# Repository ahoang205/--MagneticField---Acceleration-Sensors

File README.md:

# 🧭 Cảm Biến Từ Trường & Gia Tốc Đo Xa Không Dây (Low-Power Wireless Magnetic & Acceleration Sensing System)

Dự án thiết kế hệ thống phần cứng và phần mềm nhúng (Embedded IoT System) công suất thấp dùng để đo đạc, thu thập dữ liệu **Từ Trường 3 Trục** và **Gia Tốc / Góc Quay 6 Trục**, truyền dữ liệu đo từ xa qua mạng không dây **Wi-Fi Telemetry** về máy chủ giám sát.

---

## ⚡ Tính Năng Hệ Thống (Key Features)

- **Cảm Biến Từ Trường Độ Chính Xác Cao:** Tích hợp chip **MMC5983MA** (3-Axis Magnetometer) đo từ trường trái đất và phát hiện các biến đổi từ tính nhạy bén.
- **Cảm Biến Gia Tốc & Góc Quay Chuẩn Ô Tô:** Tích hợp IMU 6 trục **ASM330LHHTR** (Automotive Grade 6-axis IMU) đo gia tốc tuyến tính và vận tốc góc cực kỳ ổn định.
- **Khóa Mạch Công Suất Thấp (Low-Power Design):** Quản lý nguồn thông minh tối ưu điện năng tiêu thụ cho các thiết bị đo đạc chạy pin / năng lượng mặt trời.
- **Truyền Dữ Liệu Không Dây (Wi-Fi Telemetry):** Vi điều khiển **ESP32** đóng vai trò thu thập dữ liệu qua chuẩn truyền thông **I2C/SPI** và phát dữ liệu Telemetry liên tục qua Wi-Fi.

---

## 🧩 Sơ Đồ Khối Hệ Thống (System Architecture)

```mermaid
flowchart LR
    subgraph Sensors["Hệ Thống Cảm Biến"]
        S1["MMC5983MA (Từ Trường 3 Trục)"]
        S2["ASM330LHHTR (Gia Tốc & Gyro 6 Trục)"]
    end

    subgraph MCU["Xử Lý & Truyền Thông"]
        E1["ESP32 Microcontroller"]
        E2["Mạch Quản Lý Nguồn Năng Lượng Thấp"]
    end

    subgraph Output["Giám Sát Từ Xa"]
        W1["Mạng Wi-Fi Telemetry"]
        D1["Web Dashboard / Server Giám Sát"]
    end

    S1 -- "I2C Bus" --> E1
    S2 -- "I2C / SPI" --> E1
    E2 -- "Power Supply (3.3V)" --> E1
    E1 -- "UDP / MQTT / HTTP Telemetry" --> W1
    W1 --> D1
```

---

## 📊 Thông Số Kỹ Thuật (Specifications)

| Thông Số (Parameter) | Giá Trị (Value) | Ghi Chú (Notes) |
| :--- | :--- | :--- |
| **Vi Điều Khiển Main MCU** | `ESP32 / ESP32-WROOM-32` | Tích hợp Wi-Fi 802.11 b/g/n & Bluetooth |
| **Cảm Biến Từ Trường** | `MMC5983MA` | 0.5 mG resolution, ±8 Gauss FSR |
| **Cảm Biến IMU 6 Trục** | `ASM330LHHTR` | 3-axis Accel + 3-axis Gyro (Automotive) |
| **Chuẩn Truyền Thông Nối Tiếp** | `I2C (400kHz Fast Mode) / SPI` | Giao tiếp độ tin cậy cao |
| **Điện Áp Cấp (VCC)** | `3.3V DC` | Tích hợp LDO điện áp thấp |
| **Phần Mềm EDA Thiết Kế PCB** | `KiCad v6 / v7 / v8` | Sẵn file `.kicad_sch` & `.kicad_pcb` |

---

## 📂 Cấu Trúc Thư Mục Dự Án (Repository Structure)

```text
Magnetic_field_&_Acceleration_Sensors/
├── hardware/                         # Thiết kế phần cứng (Hardware EDA)
│   ├── schematics/                   # File bản vẽ sơ đồ nguyên lý PDF
│   │   └── schematic_Qcomment_24_12_25.pdf
│   ├── kicad/                        # Bộ file nguồn KiCad (.kicad_sch, .kicad_pcb, .kicad_pro)
│   │   ├── Low-Power Instrument.kicad_pcb
│   │   ├── Low-Power Instrument.kicad_sch
│   │   └── production/               # File Gerber gia công PCB, BOM, CPL
│   └── Dependencies/                 # Thư viện footprint & 3D STEP linh kiện
│       ├── ul_MMC5983MA/             # 3D Model & Footprints cảm biến từ trường
│       └── ul_ASM330LHHTR/           # 3D Model & Footprints cảm biến gia tốc
├── firmware/                         # Mã nguồn vi điều khiển kép (Dual MCU)
│   ├── stm32_firmware/               # Mã nguồn STM32L4xx HAL đọc mẫu cảm biến I2C/UART
│   │   ├── Core/Src/main.c           # Chương trình chính xử lý mẫu từ trường & IMU
│   │   └── supercap_test.ioc         # File cấu hình chân STM32CubeMX
│   └── esp32_wifi_telemetry/         # Mã nguồn ESP32 Arduino IDE
│       └── esp32_wifi_telemetry.ino  # Code Server Web 3D Dashboard & WebSocket Telemetry
├── docs/                             # Tài liệu kỹ thuật dự án
├── .gitignore                        # Cấu hình lọc file rác KiCad & IDE
├── LICENSE                           # Giấy phép bản quyền nguồn mở MIT
└── README.md                         # Tài liệu giới thiệu dự án
```

---

## 🛠️ Hướng Dẫn Cài Đặt & Nạp Code (Installation & Flashing Guide)

### 1. Mở & Chỉnh Sửa Phần Cứng (KiCad)
1. Cài đặt phần mềm [KiCad EDA v6+](https://www.kicad.org/).
2. Mở file `hardware/kicad/Low-Power Instrument.kicad_pro` để xem sơ đồ nguyên lý và thiết kế mạch PCB 2 lớp.

### 2. Nạp Code Cho Vi Điều Khiển ESP32
1. Mở phần mềm **Arduino IDE** (hoặc VS Code với PlatformIO).
2. Thêm bo mạch ESP32 và mở file `firmware/esp32_wifi_telemetry/esp32_wifi_telemetry.ino`.
3. Cấu hình thông số Wi-Fi (SSID, Password) và bấm **Upload** để nạp code cho ESP32.

---

## 📜 Giấy Phép (License)

Dự án được phân phối dưới giấy phép [MIT License](LICENSE) - Miễn phí sử dụng, nghiên cứu và phát triển sản phẩm thương mại.

---
*Authored by **Viet Hoang Luong**.*

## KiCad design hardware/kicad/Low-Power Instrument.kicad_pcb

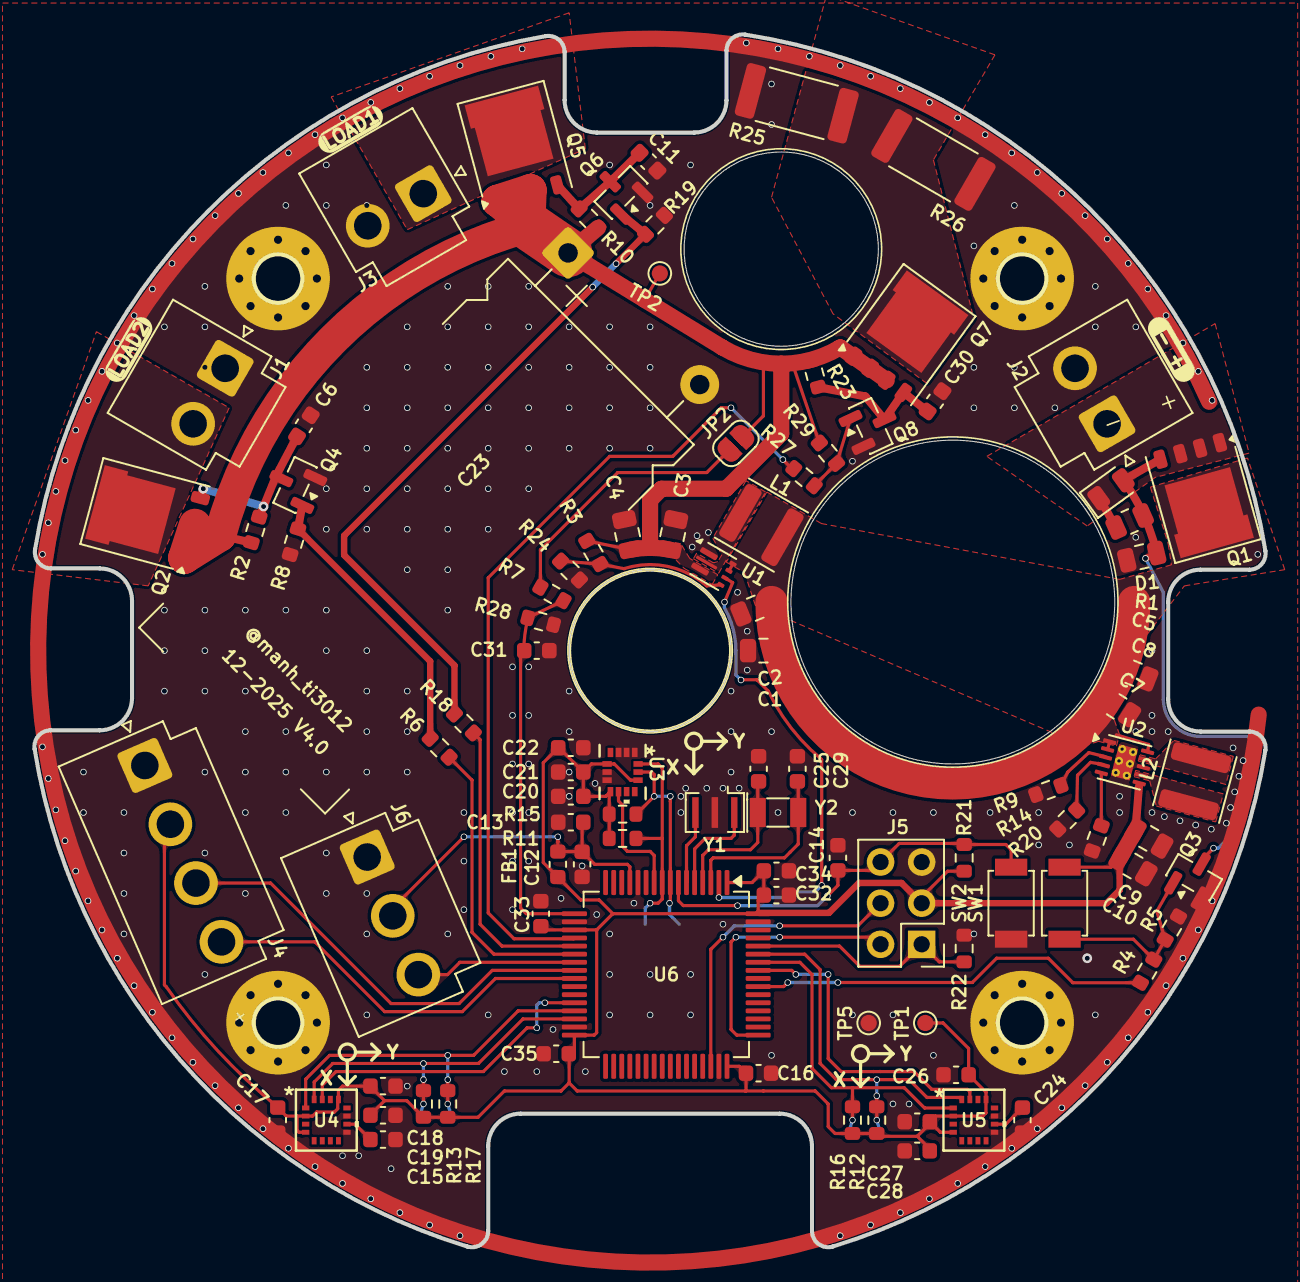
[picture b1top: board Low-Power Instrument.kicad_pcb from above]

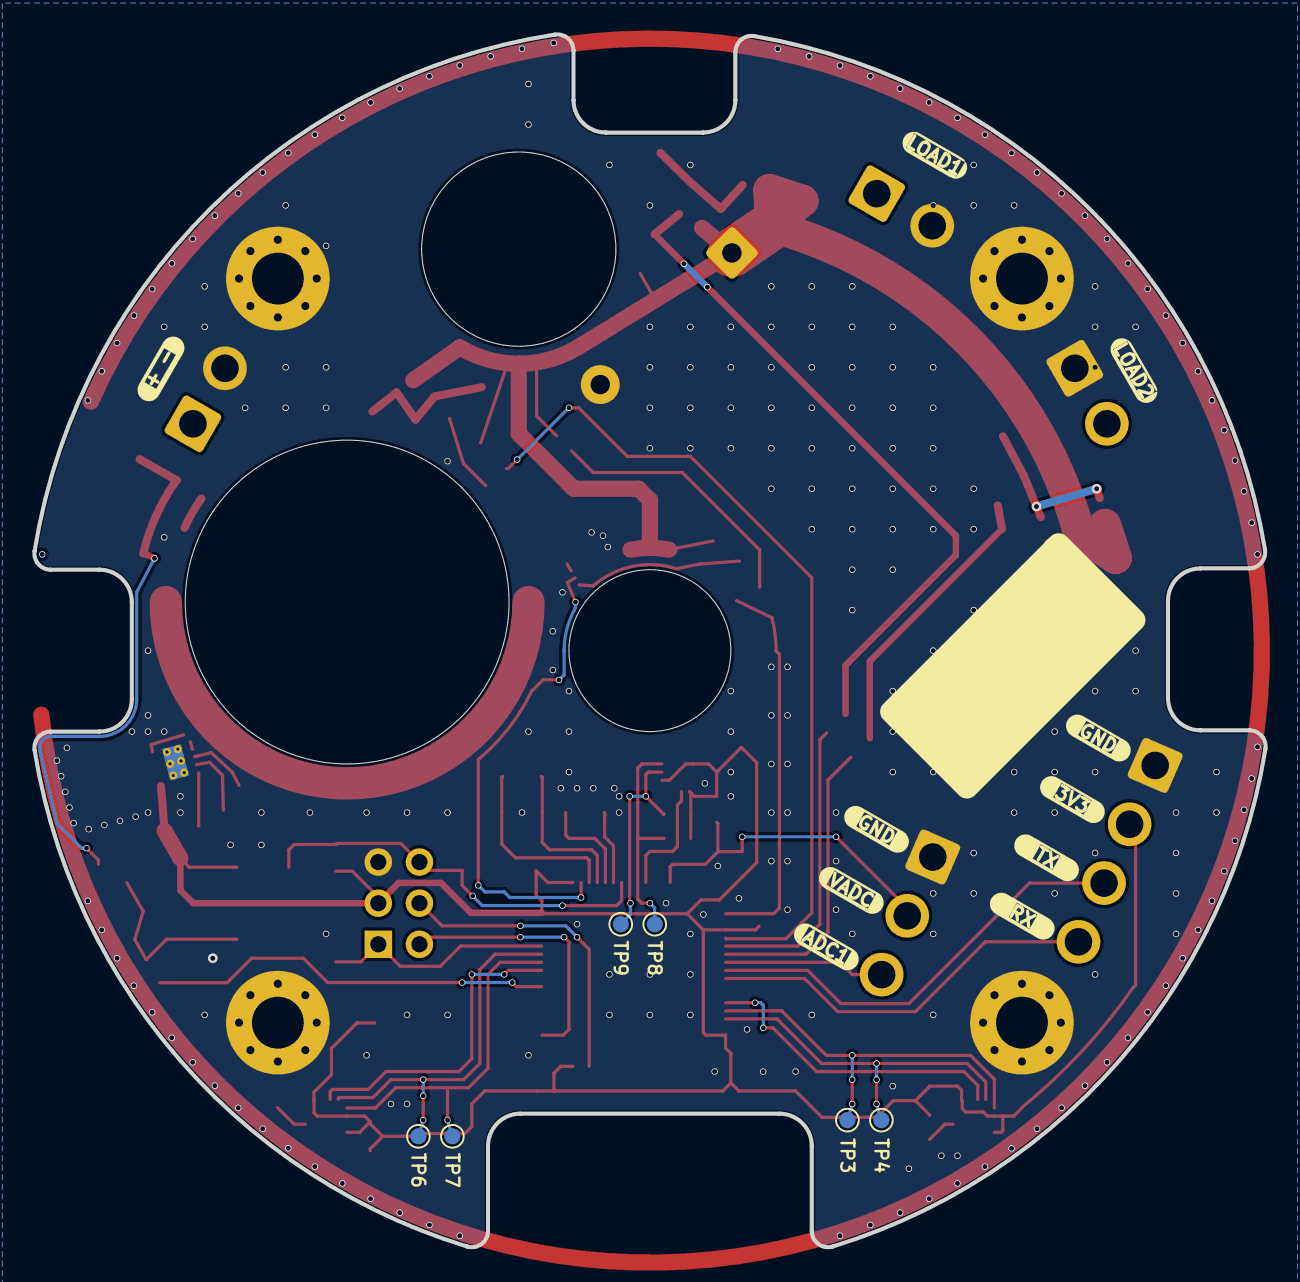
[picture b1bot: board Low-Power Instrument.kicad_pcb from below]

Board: 2 copper layers, 76.0 x 74.9 mm, 106 parts (6 on the bottom side), 53 nets.

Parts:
C1, C2, C3, C4, C5, C7, C8, C9, C10: 22uF; C_0805_2012Metric
C6, C11, C12, C14, C16, C17, C18, C20, C21, C26, C27, C30, C31, C32, C33, C34, C35: 100nF; C_0603_1608Metric
C13, C19, C22, C28: 1uF; C_0603_1608Metric
C15, C24: 10uF; C_0603_1608Metric
C23: 5F; CHP5R5L505R-TWV
C25, C29: 12.5pF; C_0603_1608Metric
D1: Diode; D_0805_2012Metric
FB1: Ferrite Bead; L_0603_1608Metric
H1, H2, H3, H4: MountingHole_Pad; MountingHole_3.2mm_M3_Pad_Via
J1, J2, J3: POWER; JST_VH_B2P-VH_1x02_P3.96mm_Vertical
J4: UART; JST_VH_B4P-VH-B_1x04_P3.96mm_Vertical
J5: DEBUG; PinHeader_2x03_P2.54mm_Vertical
J6: ADC; JST_VH_B3P-VH-B_1x03_P3.96mm_Vertical
JP2: Jumper_2_Open; SolderJumper-2_P1.3mm_Open_RoundedPad1.0x1.5mm
L1: 1uH; L_APV_ANR4020
L2: 2.2uH; L_APV_ANR4020
Q1, Q2, Q5, Q7: DON60P03; PQFN-8-EP_6x5mm_P1.27mm_Generic
Q3, Q4, Q6, Q8: AO3400; SOT-23
R1: 100K; R_0805_2012Metric
R2, R5, R7, R8, R10, R19, R21, R22, R23, R29: 100K; R_0603_1608Metric
R3: 732K; R_0603_1608Metric
R4, R6, R18, R27: 10K; R_0603_1608Metric
R9, R20: 36.5K; R_0603_1608Metric
R11, R12, R13, R15, R16, R17: 4.7K; R_0603_1608Metric
R14: 1.15K; R_0603_1608Metric
R24, R28: 200K; R_0603_1608Metric
R25, R26: 100R; R_2512_6332Metric
SW1, SW2: SW_Push; SW_SPST_B3U-1000P
TP1, TP2, TP3, TP4, TP5, TP6, TP7, TP8, TP9: TestPoint; TestPoint_Pad_D1.0mm
U1: TPS61022; Texas_RWU0007A_VQFN-7_2x2mm_P0.5mm
U2: TPS63900; WSON-10-1EP_2.5x2.5mm_P0.5mm_EP1.2x2mm_ThermalVias
U3: ASM330LHHTR; LGA-14L_2P5X3X0P83_STM
U4, U5: MMC5983MA; MMC5983MA_MEM
U6: STM32L476RGTx; LQFP-64_10x10mm_P0.5mm
Y1: 8Mhz; Resonator_SMD_Murata_CSTxExxV-3Pin_3.0x1.1mm
Y2: 32kHz; Crystal_SMD_3215-2Pin_3.2x1.5mm

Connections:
5V_ENABLE: U1.5 (EN), U6.2 (PC13)
+3.3V: C9.1, C10.1, C16.1, C17.1, C18.1, C19.1, C20.1, C21.1, C22.1, C26.1, C27.1, C28.1, C32.1, C33.1, C34.1, C35.1, FB1.1, J4.2, J5.3, R11.2, R12.2, R13.2, R15.2, R16.2, R17.2, R21.2, SW1.2, TP1.1, U2.6 (VOUT), U3.5 (VDD_IO), U3.8 (VDD), U3.12 (CS), U4.2 (VDD), U4.4 (SPI_CS), U4.13 (VDDIO), U5.2 (VDD), U5.4 (SPI_CS), U5.13 (VDDIO), U6.1 (VBAT), U6.19 (VDD), U6.32 (VDD), U6.48 (VDDUSB), U6.64 (VDD)
+5V: C3.1, C4.1, C23.1, JP2.2 (B), Q2.1 (S), Q2.2 (S), Q2.3 (S), Q5.1 (S), Q5.2 (S), Q5.3 (S), Q7.1 (S), Q7.2 (S), Q7.3 (S), R2.1, R3.2, R10.1, R23.1, R29.2, TP2.1, U1.3 (VOUT)
+BATT: D1.1 (K), J2.1, Q1.1 (S), Q1.2 (S), Q1.3 (S), R1.1
ADC1: J6.3, U6.23 (PA7)
BOOT0: J5.1, R22.2, U6.60 (BOOT0)
DISCHARGE: R27.1, U6.20 (PA4)
GND: C1.2, C2.2, C3.2, C4.2, C5.2, C6.2, C7.2, C8.2, C9.2, C10.2, C11.2, C12.2, C13.2, C14.1, C15.2, C16.2, C17.2, C18.2, C19.2, C20.2, C21.2, C22.2, C23.2, C24.2, C25.2, C26.2, C27.2, C28.2, C29.1, C30.2, C31.2, C32.2, C33.2, C34.2, C35.2, H1.1, H2.1, H3.1, H4.1, J1.1, J2.2, J3.2, J4.1, J5.5, J6.1, Q3.2 (S), Q4.2 (S), Q6.2 (S), Q8.2 (S), R5.2, R7.1, R8.2, R9.2, R14.2, R19.2, R20.2, R22.1, R25.2, R26.2, R28.2, SW2.2, TP5.1, U1.1 (GND), U2.8 (GND), U2.11 (GND), U3.1 (SDO/SA0), U3.2 (RES), U3.3 (RES), U3.6 (GND), U3.7 (GND), U4.9 (GND), U4.11 (GND), U5.9 (GND), U5.11 (GND), U6.12 (VSSA), U6.18 (VSS), U6.31 (VSS), U6.47 (VSS), U6.63 (VSS), Y1.2
I2C1_INT: U5.15 (INT), U6.57 (PB5)
I2C1_SCL: R16.1, TP7.1, U5.1 (SCL/SPI_SCK), U6.58 (PB6)
I2C1_SDA: R12.1, TP6.1, U5.16 (SDA/SPI_SDI), U6.59 (PB7)
I2C2_INT: U4.15 (INT), U6.28 (PB2)
I2C2_SCL: R17.1, TP3.1, U4.1 (SCL/SPI_SCK), U6.29 (PB10)
I2C2_SDA: R13.1, TP4.1, U4.16 (SDA/SPI_SDI), U6.30 (PB11)
I2C3_INT: U3.9 (INT2), U6.10 (PC2)
I2C3_SCL: R15.1, TP9.1, U3.13 (SCL), U6.8 (PC0)
I2C3_SDA: R11.1, TP8.1, U3.14 (SDA), U6.9 (PC1)
LOAD1_ENABLE: R18.1, U6.21 (PA5)
LOAD2_ENABLE: R6.1, U6.22 (PA6)
NRST: C14.2, J5.6, R21.1, SW2.1, U6.7 (NRST)
unnamed: C5.1, D1.2 (A), Q1.4 (G), Q3.3 (D), R1.2
unnamed: J1.2, Q2.5 (D)
unnamed: J3.1, Q5.5 (D)
unnamed: JP2.1 (A), R24.1
unnamed: C6.1, Q2.4 (G), Q4.3 (D), R2.2
unnamed: Q3.1 (G), R4.1, R5.1, SW1.1
unnamed: Q4.1 (G), R6.2, R8.1
unnamed: C11.1, Q5.4 (G), Q6.3 (D), R10.2
unnamed: Q6.1 (G), R18.2, R19.1
unnamed: Q7.5 (D), R25.1, R26.1
unnamed: C30.1, Q7.4 (G), Q8.3 (D), R23.2
unnamed: Q8.1 (G), R27.2, R29.1
unnamed: R3.1, R7.2, U1.4 (FB)
unnamed: L1.2, U1.2 (SW)
unnamed: R9.1, U2.3 (CFG1)
unnamed: R14.1, U2.4 (CFG2)
unnamed: R20.1, U2.5 (CFG3)
unnamed: L2.2, U2.9 (LX1)
unnamed: L2.1, U2.7 (LX2)
unnamed: C15.1, U4.10 (CAP)
unnamed: C24.1, U5.10 (CAP)
unnamed: C25.1, U6.3 (PC14), Y2.2
unnamed: C29.2, U6.4 (PC15), Y2.1
unnamed: U6.5 (PH0), Y1.1
unnamed: U6.6 (PH1), Y1.3
POWER_ENABLE: R4.2, U6.55 (PB3)
SWCLK: J5.2, U6.49 (PA14)
SWDIO: J5.4, U6.46 (PA13)
UART3_RX: J4.4, U6.25 (PC5)
UART3_TX: J4.3, U6.24 (PC4)
VDC: C1.1, C2.1, C7.1, C8.1, L1.1, Q1.5 (D), U1.6 (MODE), U1.7 (VIN), U2.1 (EN), U2.2 (SEL), U2.10 (VIN)
VDDA: C12.1, C13.1, FB1.2, J6.2, U6.13 (VDDA)
V_SENSE: C31.1, R24.2, R28.1, U6.17 (PA3)

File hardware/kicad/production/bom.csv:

Designator,Footprint,Quantity,Value,LCSC Part #
"C1, C10, C2, C3, C4, C5, C7, C8, C9",0805,9,22uF,
"C11, C12, C14, C16, C17, C18, C20, C21, C26, C27, C30, C31, C32, C33, C34, C35, C6",0603,17,100nF,
"C13, C19, C22, C28",0603,4,1uF,
"C15, C24",0603,2,10uF,
C23,CHP5R5L505R-TWV,1,5F,
"C25, C29",0603,2,12.5pF,
D1,0805,1,Diode,
FB1,0603,1,Ferrite Bead,
"J1, J2, J3",JST_VH_B2P-VH_1x02_P3.96mm_Vertical,3,POWER,
J4,JST_VH_B4P-VH-B_1x04_P3.96mm_Vertical,1,UART,
J5,PinHeader_2x03_P2.54mm_Vertical,1,DEBUG,
J6,JST_VH_B3P-VH-B_1x03_P3.96mm_Vertical,1,ADC,
L1,L_APV_ANR4020,1,1uH,
L2,L_APV_ANR4020,1,2.2uH,
"Q1, Q2, Q5, Q7",PQFN-8-EP_6x5mm_P1.27mm_Generic,4,DON60P03,
"Q3, Q4, Q6, Q8",SOT-23,4,AO3400,
R1,0805,1,100K,
"R10, R19, R2, R21, R22, R23, R29, R5, R7, R8",0603,10,100K,
"R11, R12, R13, R15, R16, R17",0603,6,4.7K,
R14,0603,1,1.15K,
"R18, R27, R4, R6",0603,4,10K,
"R20, R9",0603,2,36.5K,
"R24, R28",0603,2,200K,
"R25, R26",2512,2,100R,
R3,0603,1,732K,
"SW1, SW2",SW_SPST_B3U-1000P,2,SW_Push,
U1,Texas_RWU0007A_VQFN-7_2x2mm_P0.5mm,1,TPS61022,
U2,WSON-10-1EP_2.5x2.5mm_P0.5mm_EP1.2x2mm_ThermalVias,1,TPS63900,
U3,LGA-14L_2P5X3X0P83_STM,1,ASM330LHHTR,
"U4, U5",MMC5983MA_MEM,2,MMC5983MA,
U6,LQFP-64_10x10mm_P0.5mm,1,STM32L476RGTx,
Y1,Resonator_SMD_Murata_CSTxExxV-3Pin_3.0x1.1mm,1,8Mhz,
Y2,Crystal_SMD_3215-2Pin_3.2x1.5mm,1,32kHz,

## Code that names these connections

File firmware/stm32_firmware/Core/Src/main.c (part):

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  HAL_GPIO_WritePin(GPIOC, V5_enable_Pin, GPIO_PIN_SET);
  
  // Tắt xả siêu tụ điện (DISCHARGE = LOW)
  HAL_GPIO_WritePin(GPIOA, Discharge_Pin, GPIO_PIN_RESET);
  
  // Mặc định tắt các tải (Relay/LED) ban đầu
  HAL_GPIO_WritePin(GPIOA, Load1_enable_Pin | Load2_enable_Pin, GPIO_PIN_RESET);

  // Khởi tạo các cảm biến
  MMC5983_Init(&hi2c1); // Mag 2
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    if (USART3->ISR & USART_ISR_NE) {
        USART3->ICR = USART_ICR_NECF;  // Xóa lỗi nhiễu (Noise error)
    }
    // TEST PHẦN CỨNG: Nếu chập chân RX (PC5 / J4 Pin 4) xuống GND, tự động bật LED/Relay để test tiếp xúc
    if ((GPIOC->IDR & GPIO_PIN_5) == 0) {
        HAL_GPIO_WritePin(GPIOA, Load1_enable_Pin | Load2_enable_Pin, GPIO_PIN_SET);
    }
    
    if (USART3->ISR & USART_ISR_RXNE) {
        uint8_t rx_data = (uint8_t)(USART3->RDR & 0xFF);
        if (rx_data == '1') {
            // Bật cả 2 tải để kích relay đóng đèn sáng
            HAL_GPIO_WritePin(GPIOA, Load1_enable_Pin | Load2_enable_Pin, GPIO_PIN_SET);
            HAL_UART_Transmit(&huart3, (uint8_t*)"[DEBUG] STM32 RX 1\r\n", 20, 50);
        } else if (rx_data == '0') {
            // Tắt cả 2 tải
            HAL_GPIO_WritePin(GPIOA, Load1_enable_Pin | Load2_enable_Pin, GPIO_PIN_RESET);
            HAL_UART_Transmit(&huart3, (uint8_t*)"[DEBUG] STM32 RX 0\r\n", 20, 50);
        }
    }
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  __HAL_RCC_GPIOA_CLK_ENABLE();
  __HAL_RCC_GPIOB_CLK_ENABLE();

  /*Configure GPIO pin Output Level for PC13 (V5_enable) */
  HAL_GPIO_WritePin(V5_enable_GPIO_Port, V5_enable_Pin, GPIO_PIN_SET);

  /*Configure GPIO pin Output Level for Discharge and Load Switch control */
  HAL_GPIO_WritePin(Discharge_GPIO_Port, Discharge_Pin, GPIO_PIN_RESET);
  HAL_GPIO_WritePin(GPIOA, Load1_enable_Pin|Load2_enable_Pin, GPIO_PIN_RESET);

  /*Configure GPIO pin : V5_enable_Pin */
  GPIO_InitStruct.Pin = V5_enable_Pin;
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  GPIO_InitStruct.Speed = GPIO_SPEED_FREQ_LOW;
  HAL_GPIO_Init(V5_enable_GPIO_Port, &GPIO_InitStruct);

  /*Configure GPIO pins : Discharge_Pin Load1_enable_Pin Load2_enable_Pin */
  GPIO_InitStruct.Pin = Discharge_Pin|Load1_enable_Pin|Load2_enable_Pin;
  GPIO_InitStruct.Mode = GPIO_MODE_OUTPUT_PP;
  GPIO_InitStruct.Pull = GPIO_NOPULL;
  GPIO_InitStruct.Speed = GPIO_SPEED_FREQ_LOW;
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    __HAL_RCC_I2C1_CLK_ENABLE();
    __HAL_RCC_GPIOB_CLK_ENABLE();
    
    // SCL = PB6, SDA = PB7
    GPIO_InitStruct.Pin = GPIO_PIN_6|GPIO_PIN_7;
    GPIO_InitStruct.Mode = GPIO_MODE_AF_OD;
    GPIO_InitStruct.Pull = GPIO_NOPULL;
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    __HAL_RCC_I2C2_CLK_ENABLE();
    __HAL_RCC_GPIOB_CLK_ENABLE();
    
    // SCL = PB10, SDA = PB11
    GPIO_InitStruct.Pin = GPIO_PIN_10|GPIO_PIN_11;
    GPIO_InitStruct.Mode = GPIO_MODE_AF_OD;
    GPIO_InitStruct.Pull = GPIO_NOPULL;
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    __HAL_RCC_I2C3_CLK_ENABLE();
    __HAL_RCC_GPIOC_CLK_ENABLE();
    
    // SCL = PC0, SDA = PC1
    GPIO_InitStruct.Pin = GPIO_PIN_0|GPIO_PIN_1;
    GPIO_InitStruct.Mode = GPIO_MODE_AF_OD;
    GPIO_InitStruct.Pull = GPIO_NOPULL;
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    __HAL_RCC_USART3_CLK_ENABLE();
    __HAL_RCC_GPIOC_CLK_ENABLE();
    
    // TX = PC4, RX = PC5
    GPIO_InitStruct.Pin = GPIO_PIN_4|GPIO_PIN_5;
    GPIO_InitStruct.Mode = GPIO_MODE_AF_PP;
    GPIO_InitStruct.Pull = GPIO_NOPULL;
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
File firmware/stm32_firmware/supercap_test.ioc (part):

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Mcu.Name=STM32L476R(C-E-G)Tx
Mcu.Package=LQFP64
Mcu.UserName=STM32L476RGTx
PA4.GPIOParameters=GPIO_Label
PA4.GPIO_Label=Discharge
PA4.Signal=GPIO_Output
PA5.GPIOParameters=PinState,GPIO_Label
PA5.GPIO_Label=Load1_enable
PA5.PinState=GPIO_PIN_SET
PA5.Signal=GPIO_Output
PA6.GPIOParameters=PinState,GPIO_Label
PA6.GPIO_Label=Load2_enable
PA6.PinState=GPIO_PIN_SET
PA6.Signal=GPIO_Output
PC13.GPIOParameters=PinState,GPIO_Label
PC13.GPIO_Label=V5_enable
PC13.PinState=GPIO_PIN_SET
PC13.Signal=GPIO_Output
RCC.HSE_VALUE=8000000
board=custom

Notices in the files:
README.md:
License: MIT
